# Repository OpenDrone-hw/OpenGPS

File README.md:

# OpenGPS

OpenGPS is a compact GNSS and magnetometer board for the OpenDrone hardware line, designed for small FPV aircraft including the OpenFrame 3" and 5" platforms. The initial 25 x 25 mm PCB design combines a u-blox MAX-M10S receiver, passive ceramic patch antenna, and optional I2C compass. Position data is sent to the flight controller over UART; the magnetometer uses I2C.

## Specifications

| Specification | Value |
|---|---|
| Board size | 25 x 25 mm |
| PCB | 4 layers, 1.6 mm FR-4 |
| GNSS receiver | u-blox MAX-M10S-00B |
| Antenna | Abracon APAE1575R1820ABDC1-T, passive 1575.42 MHz ceramic patch |
| Magnetometer | QST QMC5883P, optional I2C compass |
| Power input | 5 V nominal |
| Local supply | 3.3 V, TI TPS7A2033PDBVR low-noise LDO |
| External interface | 6-pin JST-SH: power, ground, UART, I2C |
| RF interconnect | 50 ohm grounded coplanar waveguide, L1 signal / L2 ground |
| PCB stackup | JLCPCB JLC04161H-7628 reference |

## Hardware design

The MAX-M10S receives GNSS signals from the sky-facing ceramic patch on the back of the PCB. A three-element RF matching footprint (C6-R3-C7) connects the antenna feed to RF_IN; the initial assembly uses a 0 ohm series resistor and leaves both shunt capacitors unpopulated.

A local TPS7A2033 regulator supplies 3.3 V to the GNSS receiver and QMC5883P magnetometer. The GPS UART and compass I2C bus are brought out through the six-pin connector. The compass is optional from the flight controller's perspective and should be assessed for interference once mounted on an aircraft.

The four-layer arrangement uses components and the RF trace on L1, a continuous reference ground on L2, power/utility routing on L3, and a ground plane with the ceramic patch on L4. The antenna was selected for published characterization on a 22 x 22 mm ground plane; performance in this finished assembly has not yet been measured.

## Connector pinout

J1 is a six-pin JST-SH connector (SM06B-SRSS-TBLFSN). Signal names below are from the **OpenGPS board's perspective**.

| Pin | Signal | Function |
|---|---|---|
| 1 | `+5V_IN` | Input power |
| 2 | `GND` | Ground |
| 3 | `UART_RX` | Data from flight controller TX to GNSS RXD |
| 4 | `UART_TX` | Data from GNSS TXD to flight controller RX |
| 5 | `I2C_SDA` | Magnetometer data |
| 6 | `I2C_SCL` | Magnetometer clock |

Check the flight controller's connector orientation and voltage supply before connecting a cable. UART TX and RX must cross between the two boards.

## Design files

The native KiCad 10 files live in [`hardware/`](hardware/):

- `OpenGPS.kicad_pro`, `OpenGPS.kicad_sch`, and `OpenGPS.kicad_pcb`
- `OpenGPS.kicad_dru` for project-specific design rules
- `lib.kicad_sym`, `lib.pretty/`, and `lib.3dshapes/` for project-local components
- `KiCad-Library/`, the OpenDrone shared library submodule

See [`AGENTS.md`](AGENTS.md) for the architecture, layout parameters, parts, and reproducible checks. Clone with submodules when working locally.

## Verification and contribution

The designer reported a clean PCB DRC after layout. The copied GitHub project still requires a recorded final ERC and DRC (including schematic/PCB parity), component sourcing review, and physical prototype validation. No antenna S11, acquisition, C/N0, compass interference, or flight-test results are claimed for this revision.

Contributions and design reviews are welcome, especially for antenna tuning, magnetometer placement, 3"/5" mechanical integration, and prototype measurements. Coordinate concurrent KiCad changes on [OpenDrone Discord](https://discord.gg/v3sWmTcx3R) and follow [CONTRIBUTING.md](CONTRIBUTING.md).

## Licence

Hardware licensed under [CERN-OHL-S-2.0](https://ohwr.org/cern_ohl_s_v2.txt); see [LICENSE](LICENSE).

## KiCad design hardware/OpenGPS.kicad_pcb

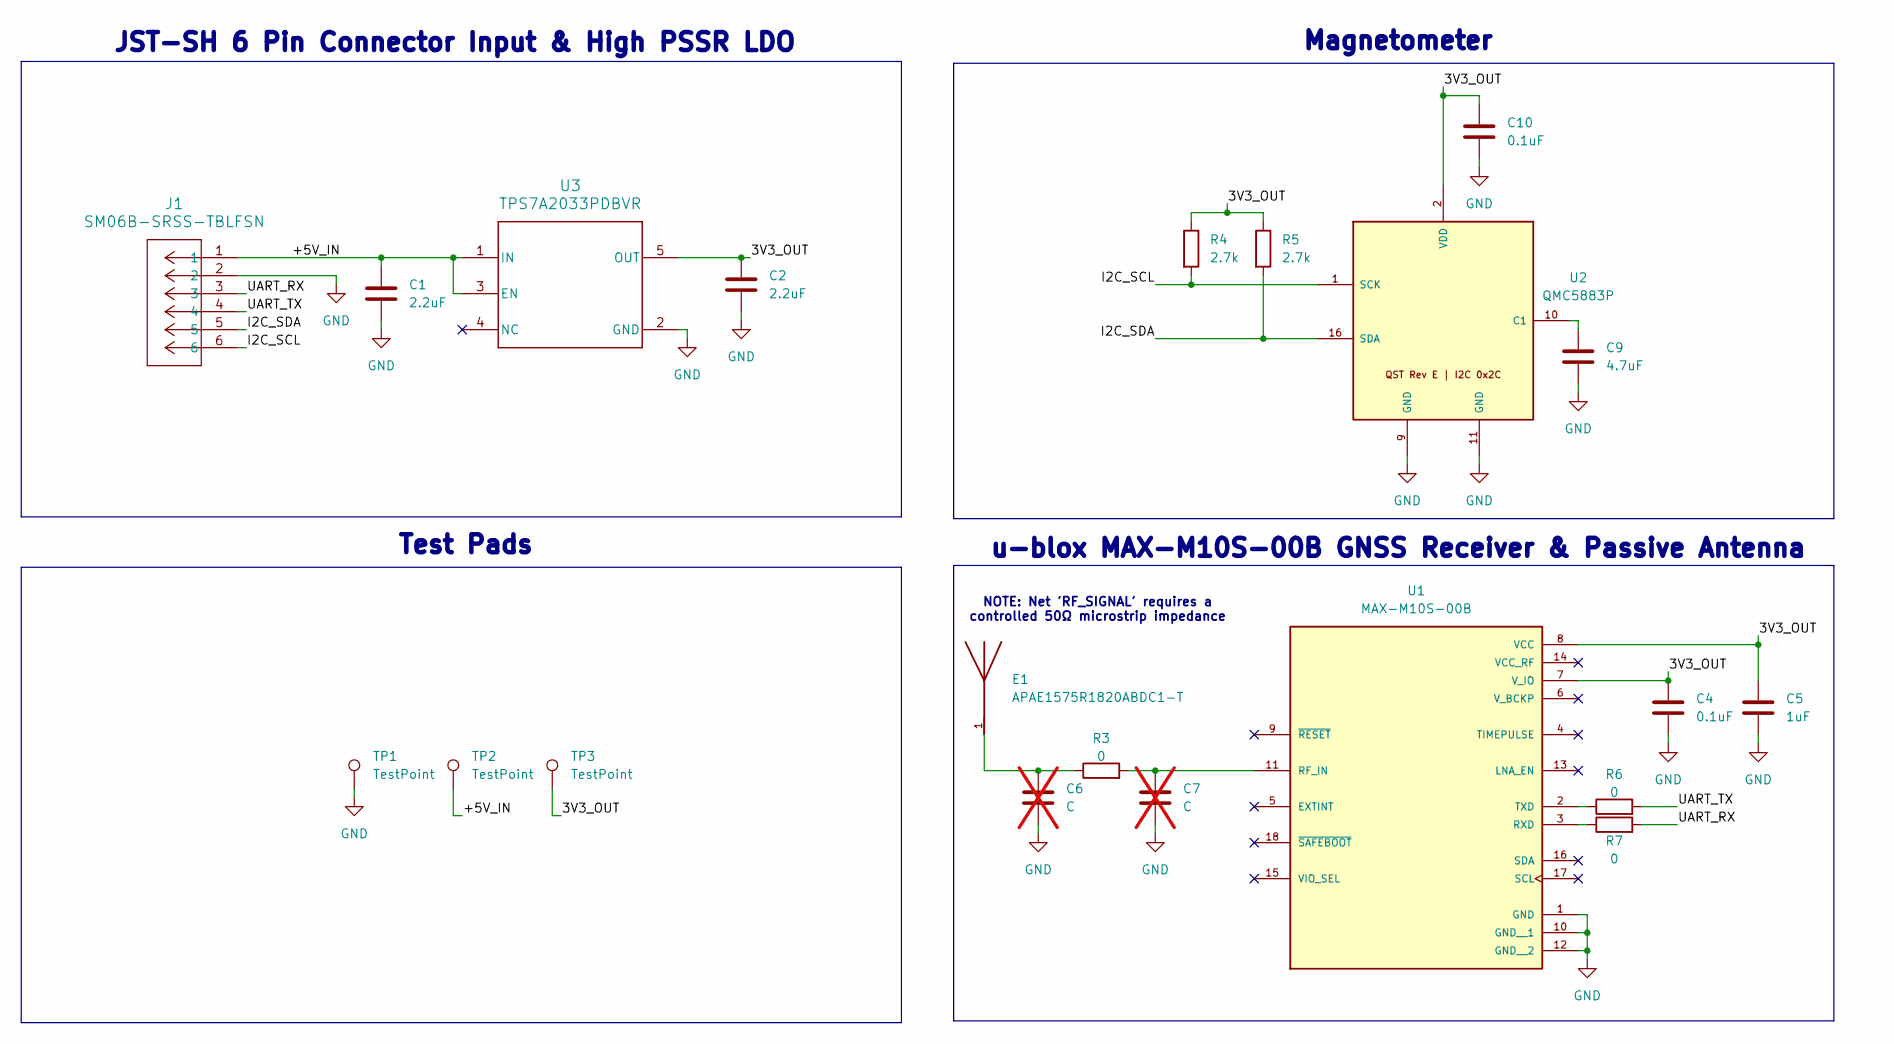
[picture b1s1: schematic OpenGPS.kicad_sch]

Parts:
C1, C2: 2.2uF; C_0402_1005Metric
C4, C10: 0.1uF; C_0402_1005Metric
C5: 1uF; C_0402_1005Metric
C6, C7: C; C_0402_1005Metric; not fitted
C9: 4.7uF; C_0402_1005Metric
E1: APAE1575R1820ABDC1-T
J1: SM06B-SRSS-TBLFSN; SM06B-SRSS-TB
R3, R6, R7: 0; R_0402_1005Metric
R4, R5: 2.7k; R_0402_1005Metric
TP1, TP2, TP3: TestPoint; TestPoint_Pad_1.0x1.0mm
U1: MAX-M10S-00B; PARTREV C1
U2: QMC5883P
U3: TPS7A2033PDBVR

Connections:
/3V3_OUT: C2.1, C4.1, C5.1, C10.1, R4.1, R5.1, TP3.1 (1_1), U1.7 (V_IO), U1.8 (VCC), U2.2 (VDD), U3.5 (OUT)
/+5V_IN: C1.1, J1.1, TP2.1 (1_1), U3.1 (IN), U3.3 (EN)
/I2C_SCL: J1.6, R4.2, U2.1 (SCK)
/I2C_SDA: J1.5, R5.2, U2.16 (SDA)
/UART_RX: J1.3, R7.2
/UART_TX: J1.4, R6.2
GND: C1.2, C2.2, C4.2, C5.2, C6.2, C7.2, C9.2, C10.2, J1.2, TP1.1 (1_1), U1.1 (GND), U1.10 (GND__1), U1.12 (GND__2), U2.9 (GND), U2.11 (GND), U3.2 (GND)
unnamed: C6.1, E1.1, R3.1
unnamed: C7.1, R3.2, U1.11 (RF_IN)
unnamed: R7.1, U1.3 (RXD)
unnamed: R6.1, U1.2 (TXD)
unnamed: C9.1, U2.10 (C1)

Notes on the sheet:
Test Pads
NOTE: Net 'RF_SIGNAL' requires a controlled 50Ω microstrip impedance
u-blox MAX-M10S-00B GNSS Receiver & Passive Antenna
JST-SH 6 Pin Connector Input & High PSSR LDO
Magnetometer

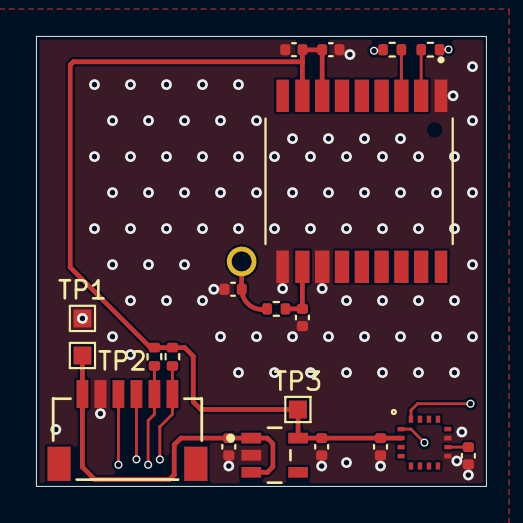
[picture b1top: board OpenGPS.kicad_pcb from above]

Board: 4 copper layers, 25.0 x 25.0 mm, 21 parts (1 on the bottom side), 12 nets.
